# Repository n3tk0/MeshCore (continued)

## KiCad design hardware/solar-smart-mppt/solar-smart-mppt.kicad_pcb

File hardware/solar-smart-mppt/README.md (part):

# solar-smart-mppt: MPPT charger + BMS 1S/2S + coulomb counter

A stand-alone power board for a solar repeater (any board: RAK, XIAO, ProMicro…), grown out
of [`../xiao-solar-lite`](../xiao-solar-lite): the same BQ25798 MPPT buck-boost charger, but the
XIAO stack is gone and a **TI MSPM0L1306** supervisor (VQFN-24, 64 KB flash) runs everything:

- drives the BQ25798 on its own I2C bus (hardware I2C1 master, PA15/PA16),
- shows itself to the repeater as an **INA260 on 0x41** (hardware I2C0 target, PA0/PA1 → J5; the ROM BSL I2C sits on the same pins),
  so MeshCore reads voltage, current and charge with `ENV_INCLUDE_INA260` and no firmware change,
- counts the charge through a 20 mΩ shunt: both shunt ends go through the zero-drift OPA0/OPA1
  (PGA up to 32×) into the 12-bit ADC,
- is the BMS: discharge FET (OD) and charge FET (OC) of an HJ8205 in the battery minus,
  short-circuit cut-off with COMP0 (32 ns) against its 8-bit DAC,
- balances a 2S LTO pack (~40 mA per cell),
- shows errors and BMS state on two LEDs on one pin.

30 × 77.5 mm (three across a 100 mm JLC panel), 2 layers, all SMD parts on the top side (JLC assembly), headers by hand.

Status v0.3 (2026-11-04): schematic, placement, routing, Gerber, JLC BOM/CPL, 3-up panel. ERC: no errors,
DRC: 0 unconnected, no clearance or short errors (only cosmetic items left, see Layout).
**Not built or tested.** Firmware for the MSPM0 (TI MSPM0 SDK, C) is a separate task.

v0.3 is the cost version (JLC quote for 15 boards was 213.63 €; v0.3 is about 150 €, see the cost
note `/mnt/project-files/notes/solar-smart-mppt-v03-cost-2026-11-04.md`):
LTC4412 → discrete ideal diode, ATtiny3226 (89 in stock at JLC) → MSPM0L1306, 2N7002DW → 2 × 2N7002,
MMDT3906 → 2 × MMBT3906, balance resistors 47 Ω → 100 Ω, C9 → 0603, RS1 → RLS12FTCR020: 7 extended
part types with a fee instead of 9.

Decisions: `/mnt/project-files/notes/solar-smart-mppt-phase1-2026-11-03.md` (phase 1) and the
answers in the project thread (phase 2).

## Connections
| Where | Pins | Notes |
|---|---|---|
| J1 SOLAR | + / − | 5–22 V panel (Voc up to 25 V), SS54 against reverse polarity, SMBJ24A TVS |
| J4 BATTERY | BATT+, BM, BATT− | 1S Li-ion / LiFePO4: BATT+ and BATT−, BM open. 2S LTO: BM = middle point |
| J3 NTC | TS / GND | optional 10k NTC (103AT); without it the MCU sets `TS_IGNORE` |
| J6 OUT | + / − | SYS through a discrete ideal diode (Q5 AO3401A + Q9/Q11 MMBT3906): battery or charger voltage, up to 5.6 V with LTO |
| J7 U | + / − | TPS63070 buck-boost, 3.3 V or 5.0 V (JP6), on/off by JP5 |
| J5 I2C host | SCL SDA 3V3 GND | to the repeater; **no pull-ups on this board** (the repeater has them); 3V3 is not used here; PA0/PA1 are 5 V tolerant open-drain pins, and the ROM bootloader (BSL, I2C) listens on them, so the host can also flash the MCU over J5: a blank chip starts the BSL by itself, a programmed one on `smppt cmd bsl`; a chip with broken firmware needs SWD (the BSL invoke pin PA18 is not on J5) |
| TP12, TP13, TP11, TP16, TP17 | 3V3M, GND, SWDIO, SWCLK, NRST | SWD on the **bottom side**, one row at 2.54 mm under the MCU band, left to right seen from the top (a 5-pin header or pogo pins from below) |

## Jumpers
| Jumper | Open | 1-2 | 2-3 |
|---|---|---|---|
| JP4 CHEM | Li-ion (PA23 follows the internal pull) | LiFePO4 (always 0) | LTO 2S (always 1) |
| JP5 EN of J7 | off | always on | MCU PA4 switches it |
| JP6 VSEL of J7 | 3.3 V | closed = 5.0 V | |
| JP3 | ship FET Q2 in use | closed = no ship FET | |

## How it works
- **Charger:** BQ25798, PROG always 1S (R1 4.7k, 750 kHz). With a 2S PROG the chip would start
  with VSYSMIN ≈ 7 V, too much for the 5.5 V parts on SYS. For LTO the MCU writes VREG 5.6 V
  (2.8 V/cell) and only then pulls ~CE low (PA17). ~CE has a pull-up to 3V3M (R4): no MCU, no charging.
  INT is not connected; the MCU polls.
- **3V3M:** HT7533 (2.5 µA) from SYS, only for the MCU and its dividers. VDD 10 µF + 100 nF,
  VCORE 470 nF, NRST 47k + 10 nF (TI minimum circuit).
- **Ideal diode (J6):** Q5 (P-FET, D at SYS, S at J6) conducts SYS → OUT through its body diode
  and is switched fully on by the PNP mirror: Q9 (diode connected, E at SYS) sets the base, Q11
  (E at OUT) pulls the Q5 gate to OUT as soon as OUT rises above SYS, so a load with its own supply
  (USB on a XIAO) cannot feed back into the battery. R43 1 MΩ / R44 470 kΩ: ~4 µA; Q5 is fully on already at 0 V drop (gate ~1.5 V at 3.7 V), and turns off when OUT is ~25 mV above SYS (up to ~0.4 A reverse for that moment).
- **BMS (Q3 HJ8205 in BATT−):** S1 = cell minus, S2 → shunt RS1 → GND.
  OD (discharge, G1) is **on by default** through R18 to BATT+, so SYS starts from the battery alone;
  the MCU turns it off through Q6 (PA26, no MCU pin sees BATT+). OC (charge, G2) is on as soon as
  3V3M is up (R20) and the MCU turns it off (PA10).
  Under-voltage uses the BQ25798 ship mode (Q2, SDRV): sun on VBUS wakes the charger, SYS comes back
  and the MCU starts again. There is **no DW01A**: over-current and short are handled by the MCU
  (OPA + COMP0 with the DAC threshold) and by the BQ25798 BATFET OCP.
- **Shunt:** 20 mΩ 1 % (±3.2 A). R21/R22 (10k) take Kelvin taps from both shunt ends, R23/R24 (1M to 3V3M)
  lift both inputs by ~33 mV so they stay above 0 V while discharging, C24 100 nF across them.
  The GND-end tap is a real Kelvin connection: R22 sits on its own net SH_K, joined to the RS1 GND
  pad by the net tie NT1, so load current in the GND pour does not shift the reading.
  SH_P runs straight down from the MCU on F.Cu with SH_N under it on B.Cu (a pair).
  SH_P → PA25 (OPA0 IN+), SH_N → PA18 (OPA1 IN+). Positive = charging.
  The offset is calibrated at zero current. Firmware: keep the OPA1 output pin off (PA16 is I2C1 SDA)
  and the OPA0 output pin PA22 unused; PA18 is also the BSL pin and sits at ~33 mV at reset (no BSL).
- **Dividers:** VBAT 1M/470k (PA24, A3), BM 1M/1M (PA21, A5), both with 100 nF. Highest ADC input is ~1.79 V
  (VBAT at 5.6 V, 2S LTO) and ~1.4 V (BM), so the firmware uses the internal 2.5 V VREF (1.4 V would clip).
- **CHEM jumper (JP4 → PA23):** read twice, once with the internal pull-up and once with the pull-down.
- **Balancing:** cell 1 (BATT−..BM) through Q7 (PA2) + R37 100 Ω; cell 2 (BM..BATT+) through the P-FET Q8
  + R41 100 Ω, its gate pulled down by Q10 (PA3). Both need push-pull pins. ~40 mA at 4.2 V, 0.18 W per 1206. Only for 2S.
- **LEDs (PA9):** high = red D6 (error), low = yellow D7 (BMS / balancing), Hi-Z = both off
  (1.8 + 1.9 V > 3.3 V, no current).
- **J7:** TPS63070 (2–16 V in), L2 2.2 µH (same part as L1) + 10 µF + 3 × 22 µF (TI table 3: Cout,eff ≥ 10 × L,eff). FB R33/R34 = 3.3 V, VSEL high adds
  R35 in parallel to R34 = 5.0 V. EN, VSEL and PS/SYNC go to VIN only through R30 10k (TI 11.1).
  PS/SYNC high = power save at light load.

## MCU pins (MSPM0L1306SRGER, VQFN-24)
| Pin | Port | Net | Use |
|---|---|---|---|
| 24 / 1 | PA0 / PA1 | SDA_E / SCL_E | I2C0 target (INA260 0x41) → J5, open-drain 5 V tolerant, also the ROM BSL I2C (SDA / SCL) |
| 12 / 11 | PA16 / PA15 | SDA_I / SCL_I | I2C1 controller → BQ25798 (R13/R14 4.7k) |
| 21 / 14 | PA25 / PA18 | SH_P / SH_N | OPA0 / OPA1 IN+ (shunt) |
| 20 / 17 | PA24 / PA21 | ADC_VBAT / ADC_VBM | ADC A3 / A5 |
| 19 | PA23 | ADC_CHEM | JP4 (digital) |
| 13 | PA17 | CE | ~CE low = charge (R4 pull-up) |
| 9 | PA10 | OC_G | R20 pull-up to 3V3M: low = charge FET off (push-pull; driving it high gives the same 3.3 V as R20) |
| 22 | PA26 | OD_CTL | discharge FET off (Q6) |
| 5 / 6 | PA2 / PA3 | BAL1 / BAL2 | balancing |
| 8 | PA9 | LED | D6 / D7 |
| 7 | PA4 | REG_CTL | J7 EN through JP5 2-3 |
| 10 | PA11 | – | not connected |
| 18 | PA22 | – | OPA0 output pin, not connected (keep the OPA0 output off the pin) |
| 15 / 16 / 2 | PA19 / PA20 / NRST | SWD | TP11 / TP16 / TP17 |
| 3 / 23 / 4, EP | VDD / VCORE / VSS | | 3V3M, 470 nF, GND (4 vias in the EP, tented from below) |

The pins are grouped by direction so every pin leaves the package without crossing: up (OC_G, LED, J7 EN),
left (CE, SWD, SH_N, VBM), down (CHEM, VBAT, SH_P, OD, VCORE, J5 SDA), right (balancing, NRST, J5 SCL).

## Layout
- Charger part = the xiao-solar-lite layout (shared cluster `../xiao-solar/tools/charger.py`).
- TPS63070 after the TI layout example: inductor above the IC, SW nodes as short copper, VIN caps left,
  VOUT caps right, PGND and GND joined under the package and taken to two vias.
- Top row: J6 OUT | J5 I2C | J7 U, ideal diode under J6, jumpers JP5/JP6 under J7.
- MCU band under the charger: MSPM0 turned 180°, its fan-out drawn by hand (`MCU_STUBS` in
  `tools/gen_pcb.py`): SWD row and HT7533 on the left, BM / VBAT dividers and JP4 under the MCU,
  balancing FETs Q8/Q10 on the right next to R37/R41.
- Shunt filter (C24, R21–R24) and net tie NT1 at the shunt RS1; SH_P on F.Cu, SH_N under it on B.Cu.
- MLCCs keep ≥ 0.9 mm from the V-cut edges (C21 and C20 turned parallel to the cut); U5, Q5, Q9, D1 pads ≥ 1.5 mm from the left edge.
- BMS, shunt, fuse at the bottom next to J4.

## Files and tools
- `tools/gen_sch.py`: schematic + BOM, writer from `../xiao-solar/tools/gen_sch.py`.
  This board has its own copy of the symbol/footprint library in `lib/` (TPS63070, HT7533 from
  easyeda2kicad); MSPM0, MMBT3906 and 2N7002 use the KiCad standard footprints.
- `tools/gen_pcb.py`: placement, TPS63070 copper, outline, pours, and the locked pre-routes:
  SYS (0.8 mm), the long MCU lines (`PRE_ROUTES`), fixed TPS63070/BQ25798 hand routes
  (`tools/hand_routes.json`, kept from v0.2) and a GND tie (short track + via into the
  B.Cu fill) for every small GND pad that the F.Cu pour cannot reach. `B_CLEAR` boxes keep
  Freerouting off B.Cu where long B lines used to cut the ground fill into islands.
- `tools/patch2.py`: own two-layer grid A* (0.1 mm grid). Used for the pre-routes and for the few
  connections Freerouting leaves open: `python3 tools/patch2.py NET X1 Y1 X2 Y2 [WIDTH]`.
- `tools/gndfix.py`, `tools/bfrag.py`: check for GND copper without a connection and tie it with a via.
- `tools/run.py <tool>` runs a shared tool from `../xiao-solar/tools` on this board:
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
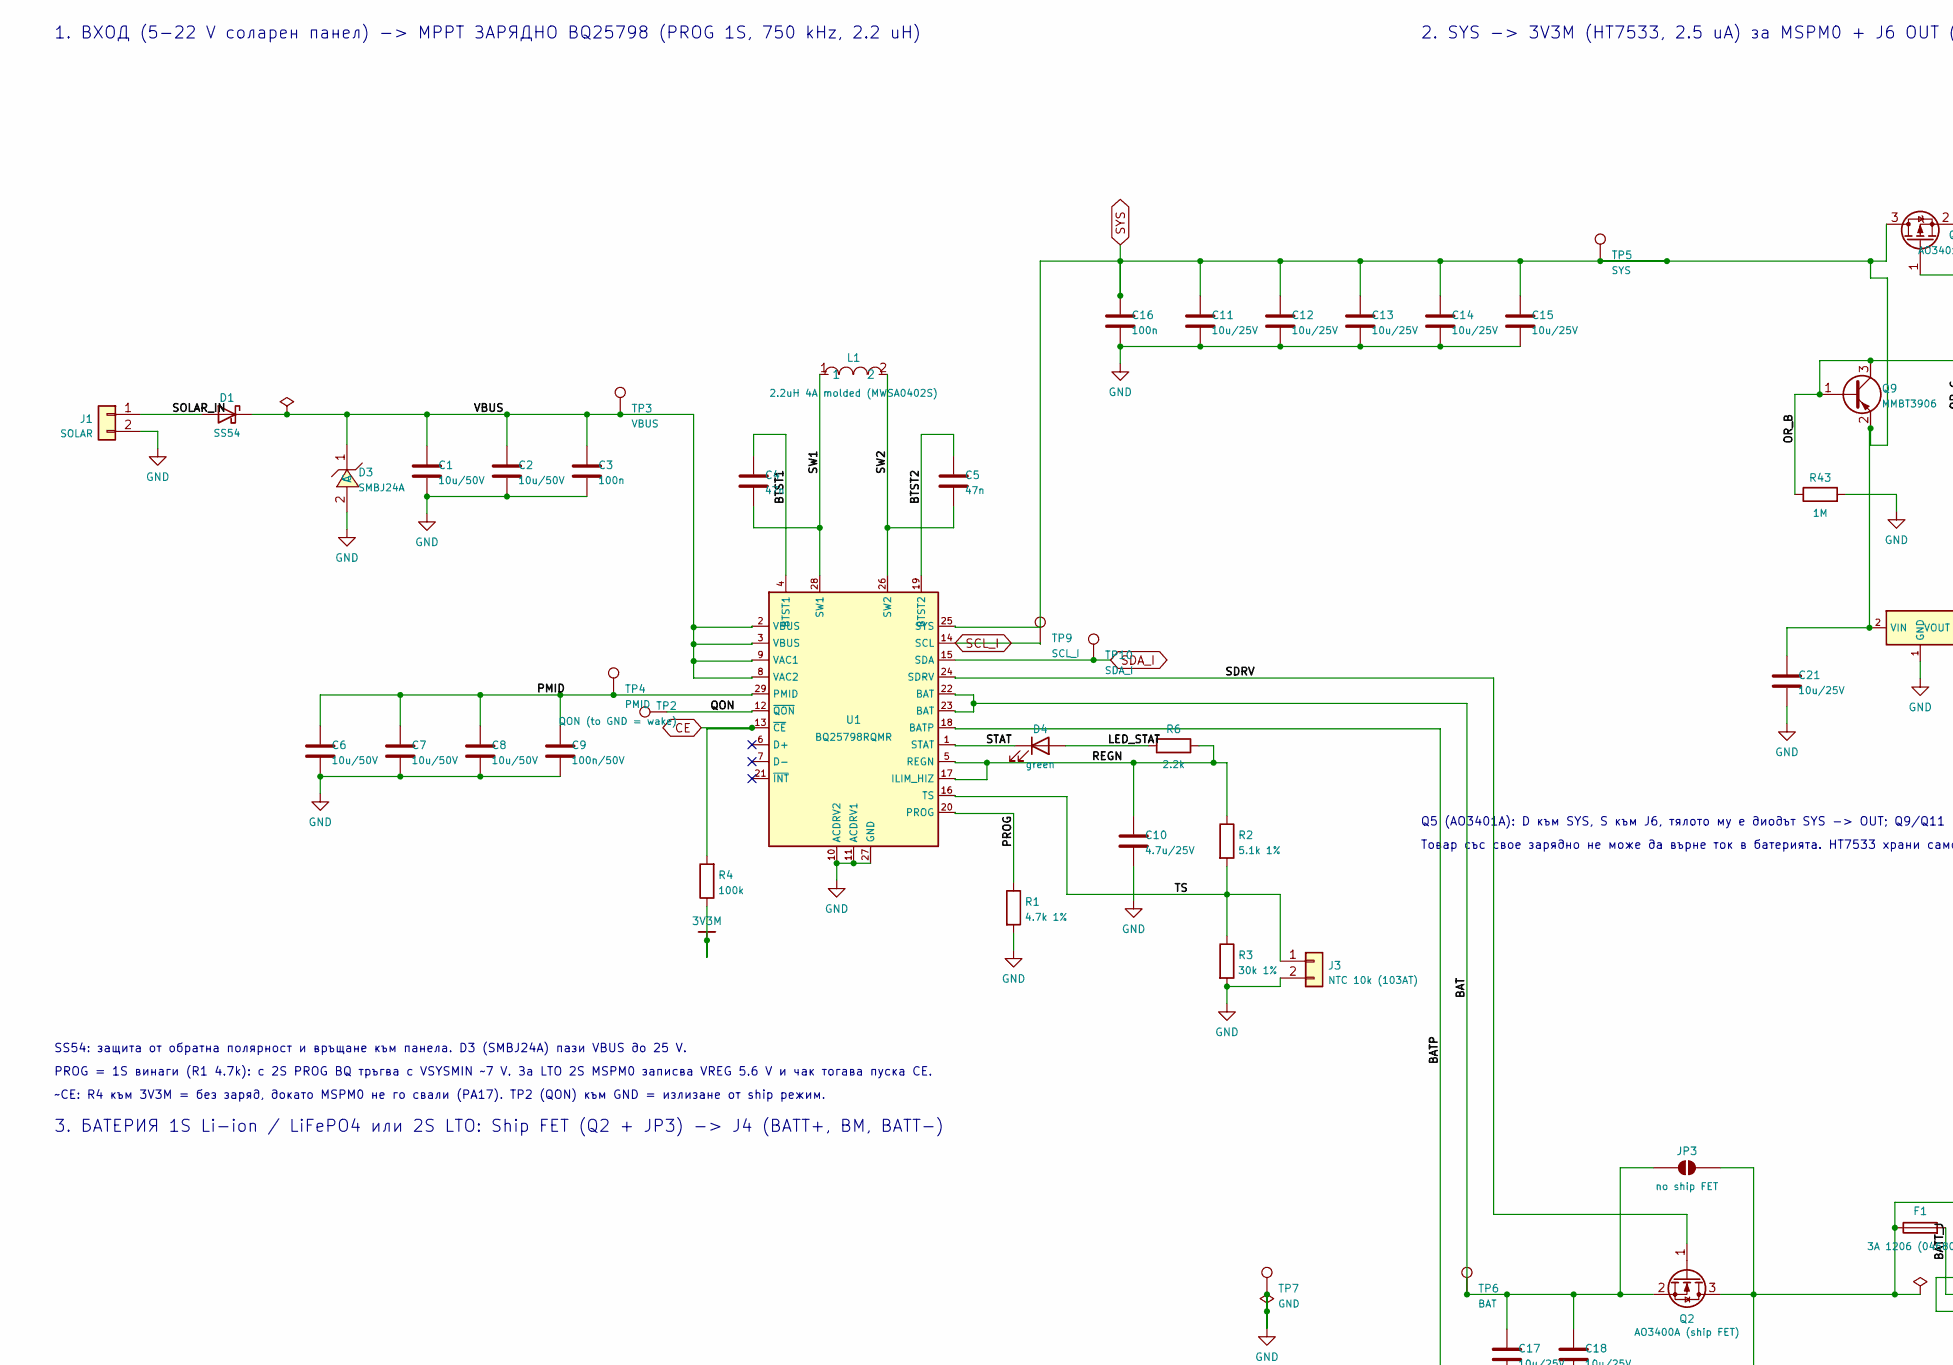
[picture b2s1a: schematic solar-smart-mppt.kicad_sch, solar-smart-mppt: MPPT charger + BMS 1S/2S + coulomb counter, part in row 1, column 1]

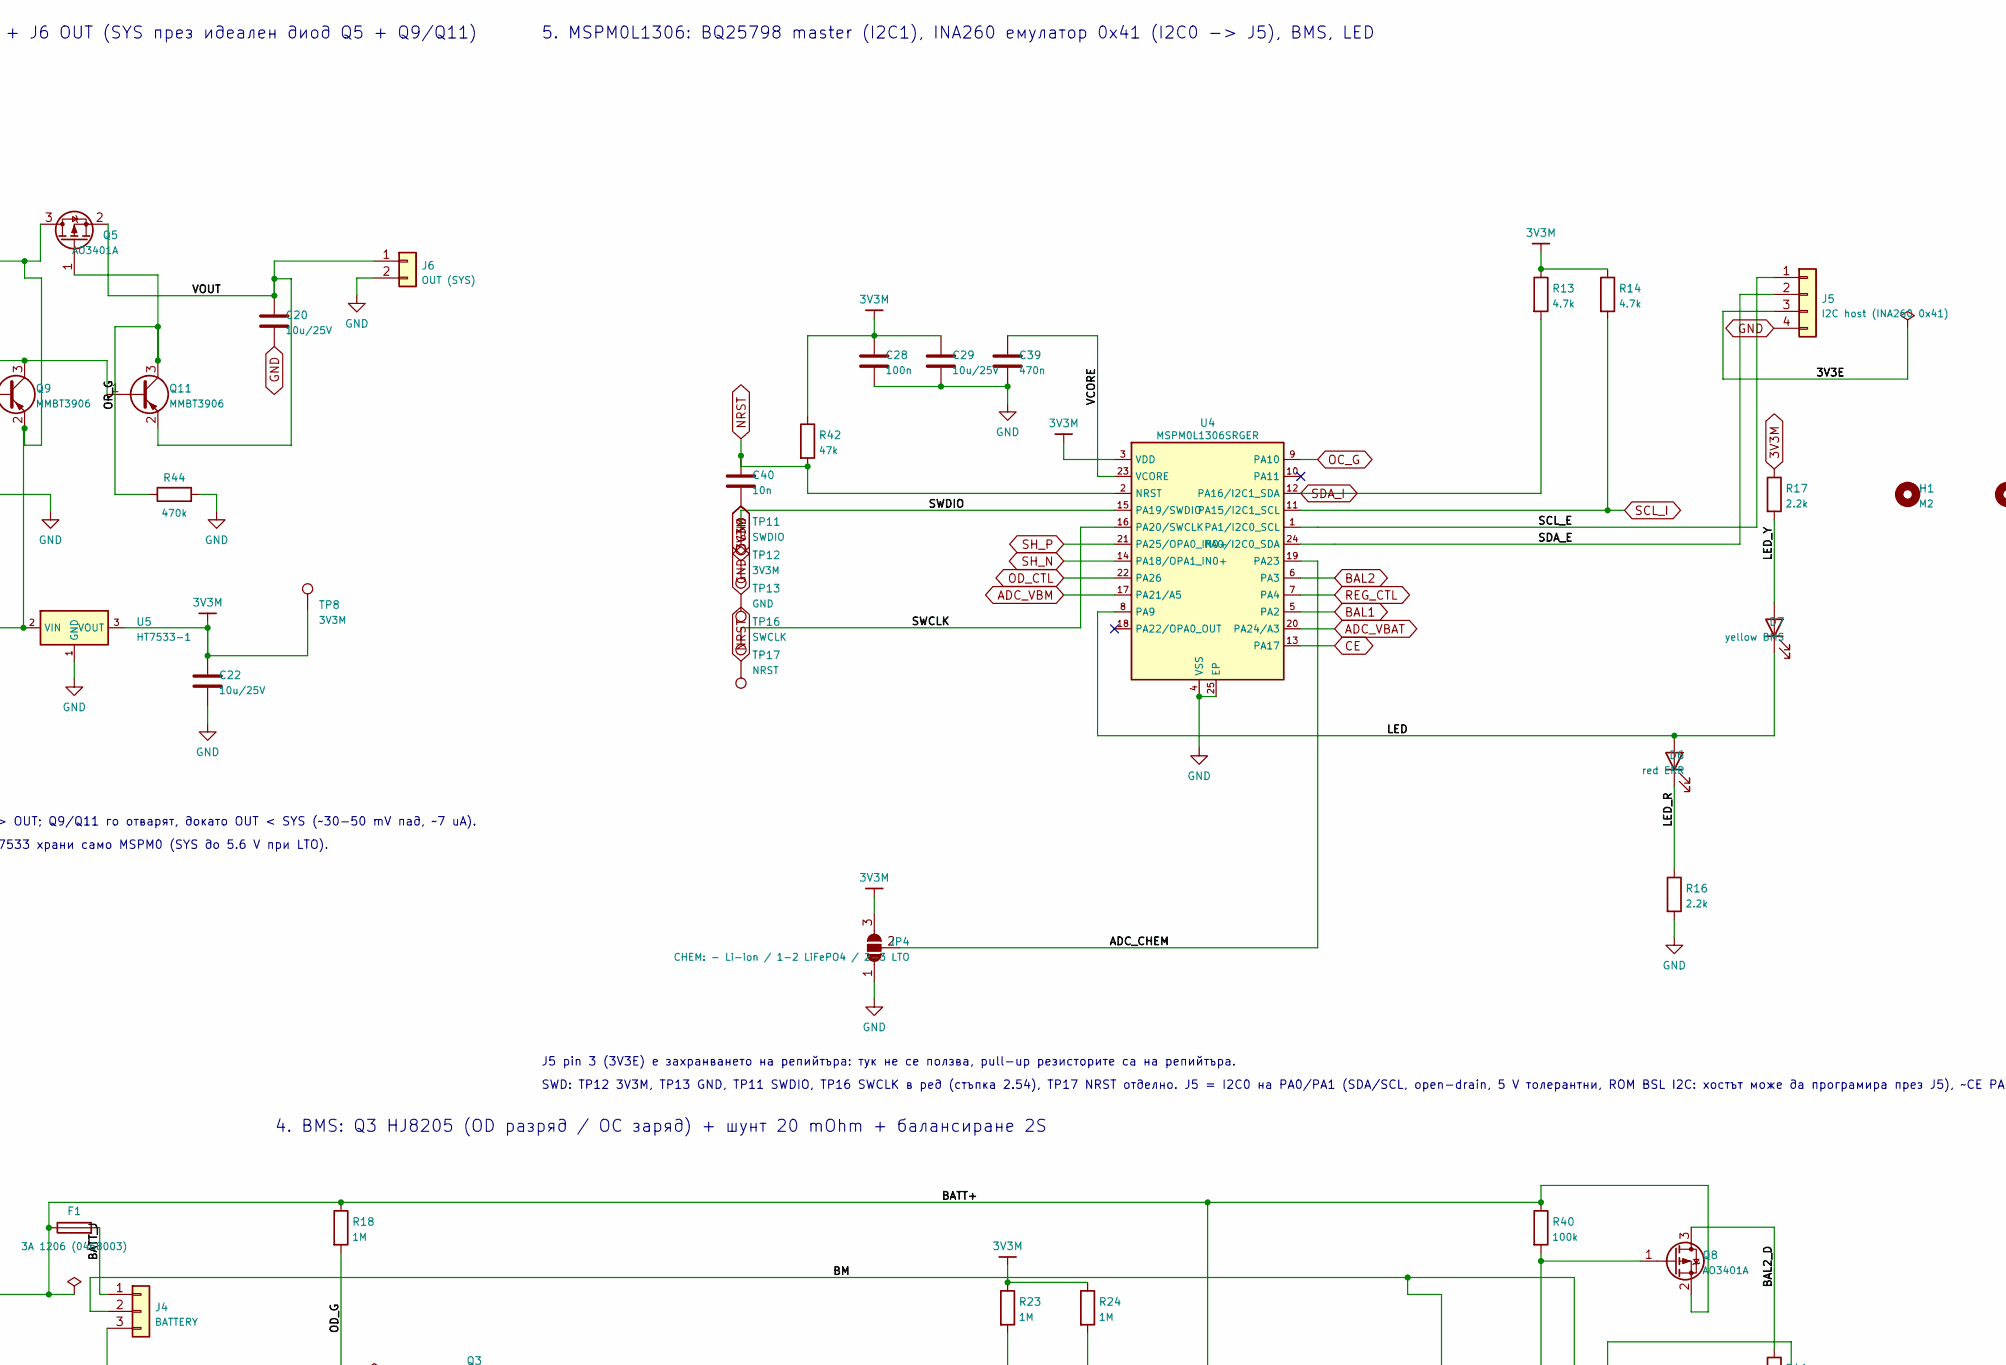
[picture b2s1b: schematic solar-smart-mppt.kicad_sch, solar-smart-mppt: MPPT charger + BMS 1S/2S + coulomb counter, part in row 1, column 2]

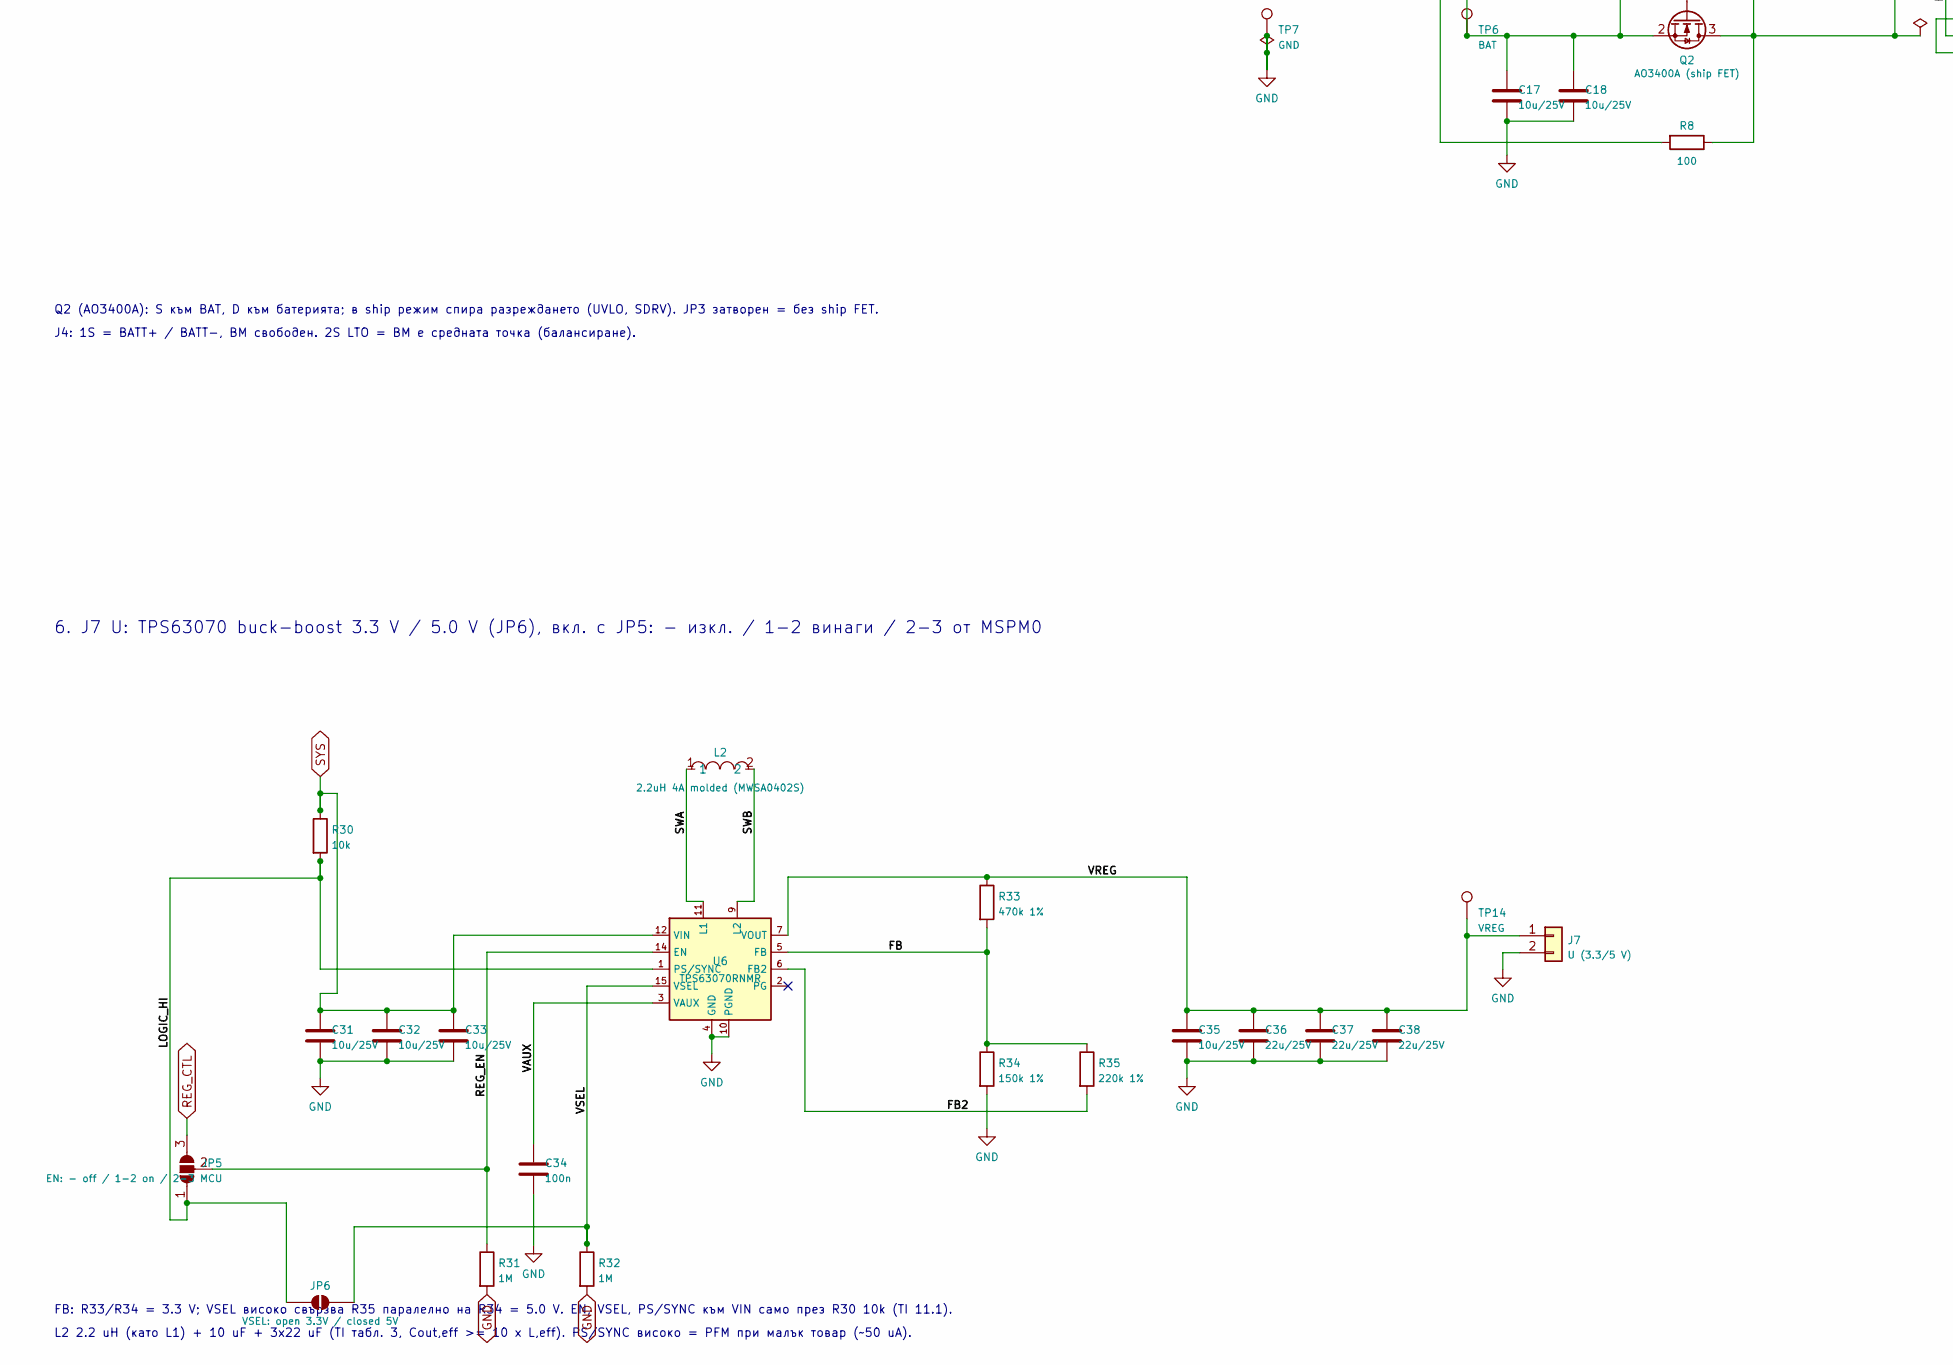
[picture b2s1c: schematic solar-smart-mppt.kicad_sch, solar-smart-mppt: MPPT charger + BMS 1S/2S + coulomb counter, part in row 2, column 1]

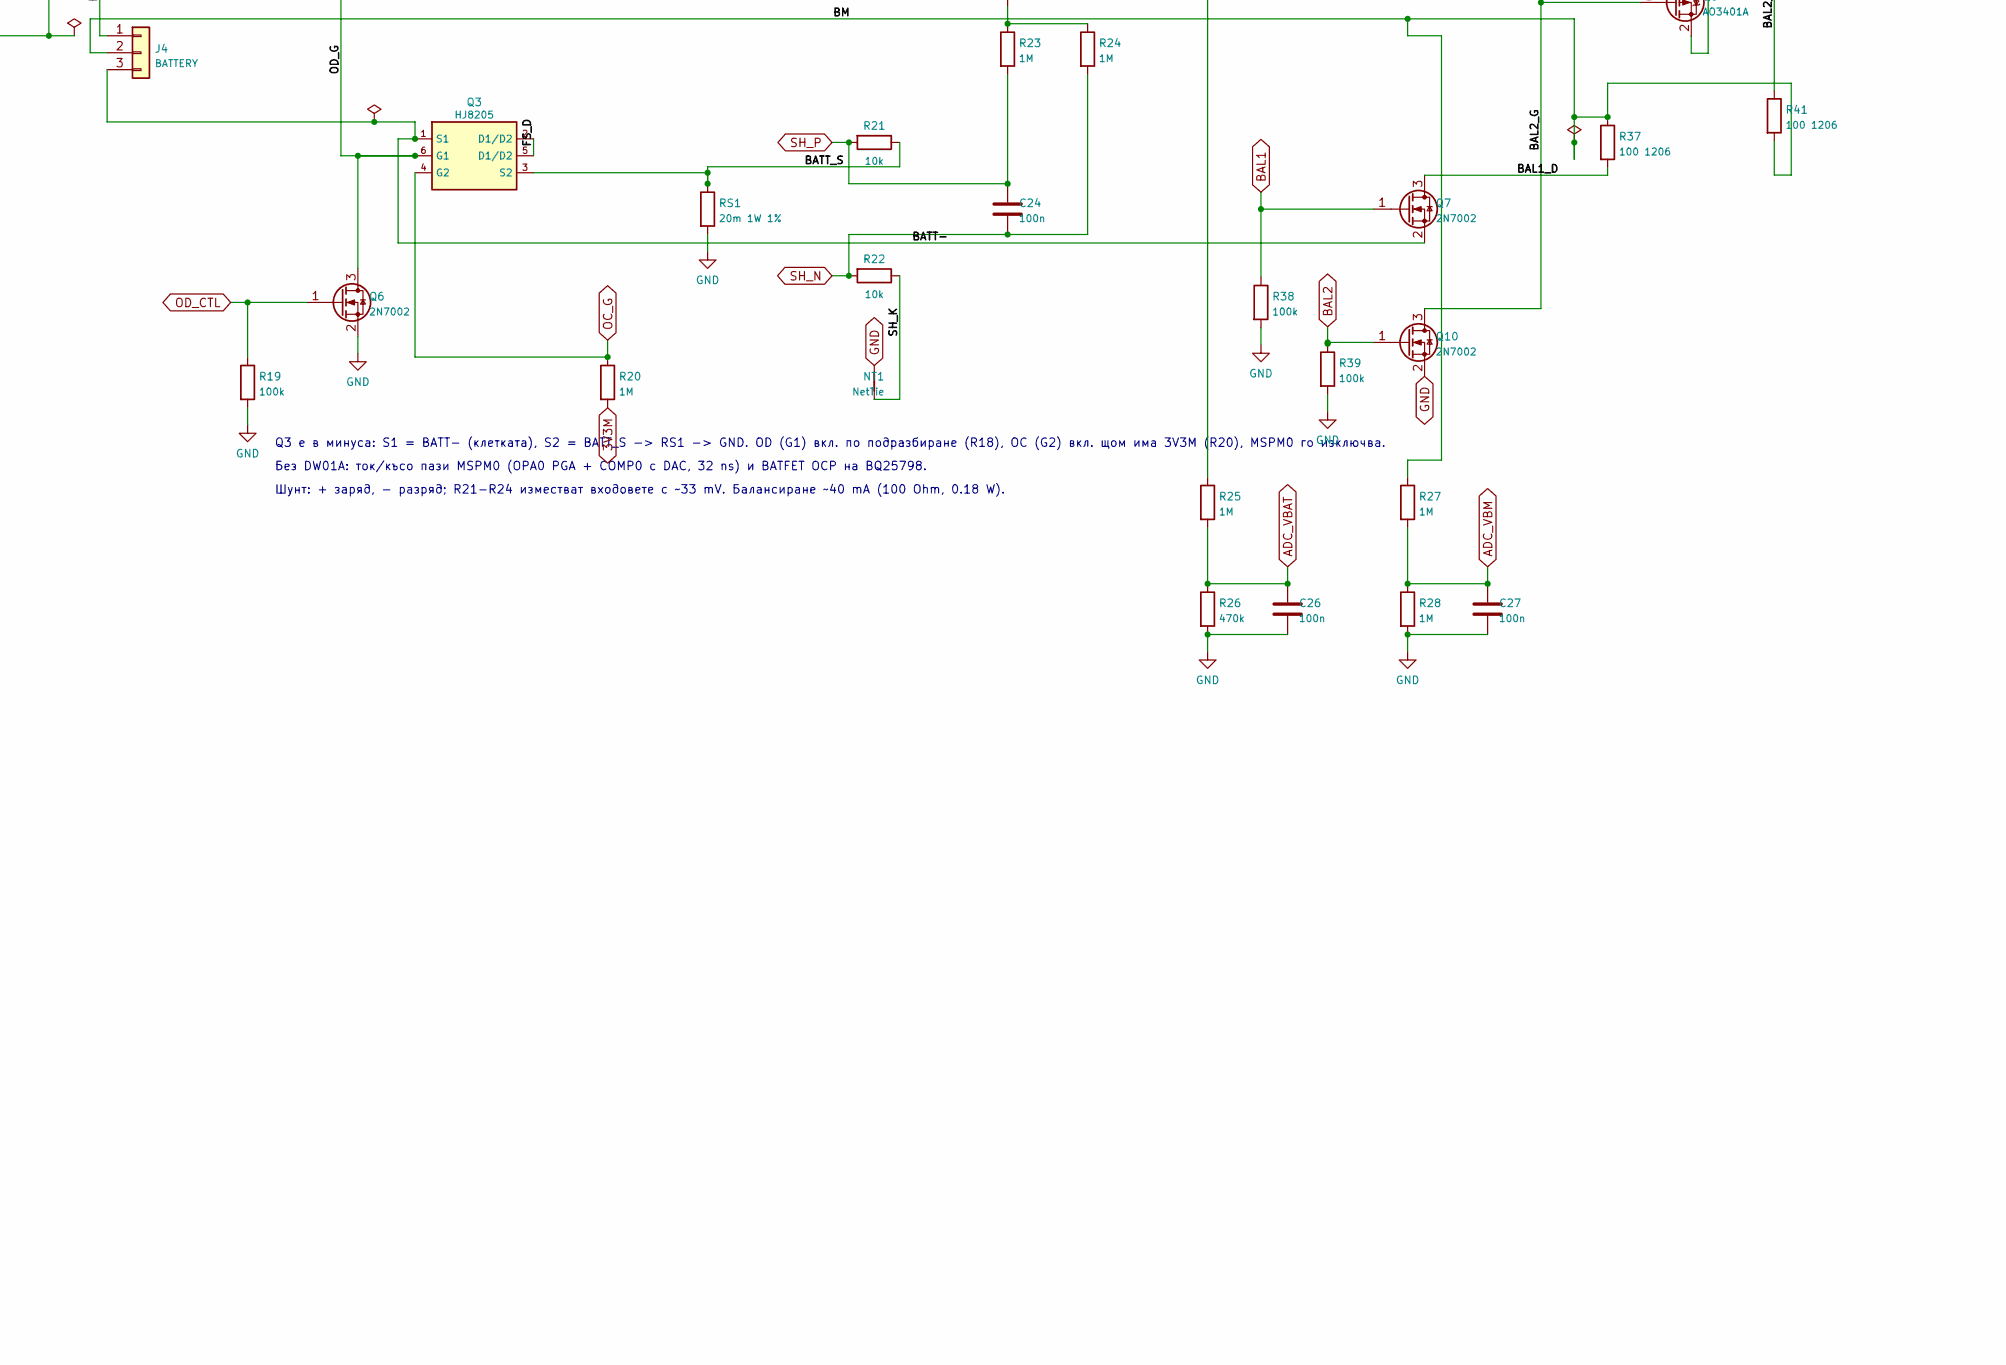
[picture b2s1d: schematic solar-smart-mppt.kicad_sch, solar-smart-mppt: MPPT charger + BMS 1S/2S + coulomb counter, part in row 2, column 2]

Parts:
C1, C2, C6, C7, C8: 10u/50V; C_1206_3216Metric; LCSC C13585
C3: 100n; C_0603_1608Metric; LCSC C14663
C4, C5: 47n; C_0603_1608Metric; LCSC C1622
C9: 100n/50V; C_0603_1608Metric; LCSC C14663
C10: 4.7u/25V; C_0805_2012Metric; LCSC C1779
C11, C12, C13, C14, C15, C17, C18, C20, C21, C22, C29, C31, C32, C33, C35: 10u/25V; C_0805_2012Metric; LCSC C15850
C16, C24, C26, C27, C28, C34: 100n; C_0402_1005Metric; LCSC C1525
C36, C37, C38: 22u/25V; C_0805_2012Metric; LCSC C45783
C39: 470n; C_0603_1608Metric; LCSC C1623
C40: 10n; C_0402_1005Metric; LCSC C15195
D1: SS54; D_SMA; LCSC C22452
D3: SMBJ24A; SMB_L4.6-W3.6-LS5.3-RD; LCSC C19077578
D4: green; LED_0805_2012Metric; LCSC C2297
D6: red ERR; LED_0805_2012Metric; LCSC C84256
D7: yellow BMS; LED_0805_2012Metric; LCSC C2296
F1: 3A 1206 (0468003); Fuse_1206_3216Metric; LCSC C41342
H1, H2: M2; MountingHole_2.2mm_M2
J1: SOLAR; PinHeader_1x02_P2.54mm_Vertical
J3: NTC 10k (103AT); PinHeader_1x02_P2.54mm_Vertical
J4: BATTERY; PinHeader_1x03_P2.54mm_Vertical
J5: I2C host (INA260 0x41); PinHeader_1x04_P2.54mm_Vertical
J6: OUT (SYS); PinHeader_1x02_P2.54mm_Vertical
J7: U (3.3/5 V); PinHeader_1x02_P2.54mm_Vertical
JP3: no ship FET; SolderJumper-2_P1.3mm_Open_RoundedPad1.0x1.5mm
JP4: CHEM: - Li-ion / 1-2 LiFePO4 / 2-3 LTO; SolderJumper-3_P1.3mm_Open_RoundedPad1.0x1.5mm
JP5: EN: - off / 1-2 on / 2-3 MCU; SolderJumper-3_P1.3mm_Open_RoundedPad1.0x1.5mm
JP6: VSEL: open 3.3V / closed 5V; SolderJumper-2_P1.3mm_Open_RoundedPad1.0x1.5mm
L1, L2: 2.2uH 4A molded (MWSA0402S); IND-SMD_L4.4-W4.2_MWSA0402S; LCSC C408335
NT1: NetTie; NetTie-2_SMD_Pad0.5mm
Q2: AO3400A (ship FET); SOT-23; LCSC C20917
Q3: HJ8205; SOT-23-6_L2.9-W1.6-P0.95-LS2.8-BL; LCSC C20069150
Q5, Q8: AO3401A; SOT-23; LCSC C15127
Q6, Q7, Q10: 2N7002; SOT-23; LCSC C8545
Q9, Q11: MMBT3906; SOT-23; LCSC C7420354
R1: 4.7k 1%; R_0603_1608Metric; LCSC C23162
R2: 5.1k 1%; R_0603_1608Metric; LCSC C23186
R3: 30k 1%; R_0603_1608Metric; LCSC C22984
R4, R19, R38, R39, R40: 100k; R_0402_1005Metric; LCSC C25741
R6, R16, R17: 2.2k; R_0402_1005Metric; LCSC C25879
R8: 100; R_0603_1608Metric; LCSC C22775
R13, R14: 4.7k; R_0402_1005Metric; LCSC C25900
R18, R20, R23, R24, R25, R27, R28, R31, R32, R43: 1M; R_0402_1005Metric; LCSC C26083
R21, R22, R30: 10k; R_0402_1005Metric; LCSC C25744
R26, R44: 470k; R_0603_1608Metric; LCSC C23178
R33: 470k 1%; R_0603_1608Metric; LCSC C23178
R34: 150k 1%; R_0603_1608Metric; LCSC C22807
R35: 220k 1%; R_0603_1608Metric; LCSC C22961
R37, R41: 100 1206; R_1206_3216Metric; LCSC C17901
R42: 47k; R_0402_1005Metric; LCSC C25792
RS1: 20m 1W 1%; R_1206_3216Metric; LCSC C163047
TP2: QON (to GND = wake); TestPoint_Pad_D1.0mm
TP3: VBUS; TestPoint_Pad_D1.0mm
TP4: PMID; TestPoint_Pad_D1.0mm
TP5: SYS; TestPoint_Pad_D1.0mm
TP6: BAT; TestPoint_Pad_D1.0mm
TP7, TP13: GND; TestPoint_Pad_D1.0mm
TP8, TP12: 3V3M; TestPoint_Pad_D1.0mm
TP9: SCL_I; TestPoint_Pad_D1.0mm
TP10: SDA_I; TestPoint_Pad_D1.0mm
TP11: SWDIO; TestPoint_Pad_D1.0mm
TP14: VREG; TestPoint_Pad_D1.0mm
TP16: SWCLK; TestPoint_Pad_D1.0mm
TP17: NRST; TestPoint_Pad_D1.0mm
U1: BQ25798RQMR; QFN-29_L4.0-W4.0-P0.40-TL-BQ25792RQMR; LCSC C2876593
U4: MSPM0L1306SRGER; VQFN-24-1EP_4x4mm_P0.5mm_EP2.45x2.45mm; LCSC C19189323
U5: HT7533-1; SOT-89-3_L4.5-W2.5-P1.50-LS4.2-BR; LCSC C14289
U6: TPS63070RNMR; VQFN-15_L3.0-W2.5-P0.50-BL; LCSC C109322

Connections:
3V3E: J5.3
3V3M: C22.1, C28.1, C29.1, JP4.3 (B), R4.1, R13.1, R14.1, R17.1, R20.2, R23.1, R24.1, R42.1, TP8.1, TP12.1, U4.3 (VDD), U5.3 (VOUT)
ADC_CHEM: JP4.2 (C), U4.19 (PA23)
ADC_VBAT: C26.1, R25.2, R26.1, U4.20 (PA24/A3)
ADC_VBM: C27.1, R27.2, R28.1, U4.17 (PA21/A5)
BAL1: Q7.1 (G), R38.1, U4.5 (PA2)
BAL1_D: Q7.3 (D), R37.2
BAL2: Q10.1 (G), R39.1, U4.6 (PA3)
BAL2_D: Q8.3 (D), R41.1
BAL2_G: Q8.1 (G), Q10.3 (D), R40.2
BAT: C17.1, C18.1, JP3.1 (A), Q2.2 (S), TP6.1, U1.22 (BAT), U1.23 (BAT)
BATP: R8.2, U1.18 (BATP)
BATT+: F1.1, JP3.2 (B), Q2.3 (D), Q8.2 (S), R8.1, R18.1, R25.1, R40.1
BATT-: J4.3, Q3.1 (S1), Q7.2 (S)
BATT_J: F1.2, J4.1
BATT_S: Q3.3 (S2), R21.1, RS1.1
BM: J4.2, R27.1, R37.1, R41.2
BTST1: C4.1, U1.4 (BTST1)
BTST2: C5.1, U1.19 (BTST2)
CE: R4.2, U1.13 (~CE), U4.13 (PA17)
FB: R33.2, R34.1, R35.1, U6.5 (FB)
FB2: R35.2, U6.6 (FB2)
FS_D: Q3.2 (D1/D2), Q3.5 (D1/D2)
GND: C1.2, C2.2, C3.2, C6.2, C7.2, C8.2, C9.2, C10.2, C11.2, C12.2, C13.2, C14.2, C15.2, C16.2, C17.2, C18.2, C20.2, C21.2, C22.2, C26.2, C27.2, C28.2, C29.2, C31.2, C32.2, C33.2, C34.2, C35.2, C36.2, C37.2, C38.2, C39.2, C40.2, D3.2 (A), J1.2, J3.2, J5.4, J6.2, J7.2, JP4.1 (A), NT1.2, Q6.2 (S), Q10.2 (S), R1.2, R3.2, R16.2, R19.2, R26.2, R28.2, R31.2, R32.2, R34.2, R38.2, R39.2, R43.2, R44.2, RS1.2, TP7.1, TP13.1, U1.10 (ACDRV2), U1.11 (ACDRV1), U1.27 (GND), U4.4 (VSS), U4.25 (EP), U5.1 (GND), U6.4 (GND), U6.10 (PGND)
LED: D6.2 (A), D7.1 (K), U4.8 (PA9)
LED_R: D6.1 (K), R16.1
LED_STAT: D4.2 (A), R6.2
LED_Y: D7.2 (A), R17.2
LOGIC_HI: JP5.1 (A), JP6.1 (A), R30.2, U6.1 (PS/SYNC)
NRST: C40.1, R42.2, TP17.1, U4.2 (NRST)
OC_G: Q3.4 (G2), R20.1, U4.9 (PA10)
OD_CTL: Q6.1 (G), R19.1, U4.22 (PA26)
OD_G: Q3.6 (G1), Q6.3 (D), R18.2
OR_B: Q9.1 (B), Q9.3 (C), Q11.1 (B), R43.1
OR_G: Q5.1 (G), Q11.3 (C), R44.1
PMID: C6.1, C7.1, C8.1, C9.1, TP4.1, U1.29 (PMID)
PROG: R1.1, U1.20 (PROG)
QON: TP2.1, U1.12 (~QON)
REGN: C10.1, R2.1, R6.1, U1.5 (REGN), U1.17 (ILIM_HIZ)
REG_CTL: JP5.3 (B), U4.7 (PA4)
REG_EN: JP5.2 (C), R31.1, U6.14 (EN)
SCL_E: J5.1, U4.1 (PA1/I2C0_SCL)
SCL_I: R14.2, TP9.1, U1.14 (SCL), U4.11 (PA15/I2C1_SCL)
SDA_E: J5.2, U4.24 (PA0/I2C0_SDA)
SDA_I: R13.2, TP10.1, U1.15 (SDA), U4.12 (PA16/I2C1_SDA)
SDRV: Q2.1 (G), U1.24 (SDRV)
SH_K: NT1.1, R22.1
SH_N: C24.2, R22.2, R24.2, U4.14 (PA18/OPA1_IN0+)
SH_P: C24.1, R21.2, R23.2, U4.21 (PA25/OPA0_IN0+)
SOLAR_IN: D1.2 (A), J1.1
STAT: D4.1 (K), U1.1 (STAT)
SW1: C4.2, L1.1, U1.28 (SW1)
SW2: C5.2, L1.2, U1.26 (SW2)
SWA: L2.1, U6.11 (L1)
SWB: L2.2, U6.9 (L2)
SWCLK: TP16.1, U4.16 (PA20/SWCLK)
SWDIO: TP11.1, U4.15 (PA19/SWDIO)
SYS: C11.1, C12.1, C13.1, C14.1, C15.1, C16.1, C21.1, C31.1, C32.1, C33.1, Q5.3 (D), Q9.2 (E), R30.1, TP5.1, U1.25 (SYS), U5.2 (VIN), U6.12 (VIN)
TS: J3.1, R2.2, R3.1, U1.16 (TS)
VAUX: C34.1, U6.3 (VAUX)
VBUS: C1.1, C2.1, C3.1, D1.1 (K), D3.1 (C), TP3.1, U1.2 (VBUS), U1.3 (VBUS), U1.8 (VAC2), U1.9 (VAC1)
VCORE: C39.1, U4.23 (VCORE)
VOUT: C20.1, J6.1, Q5.2 (S), Q11.2 (E)
VREG: C35.1, C36.1, C37.1, C38.1, J7.1, R33.1, TP14.1, U6.7 (VOUT)
VSEL: JP6.2 (B), R32.1, U6.15 (VSEL)

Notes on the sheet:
1. ВХОД (5-22 V соларен панел) -> MPPT ЗАРЯДНО BQ25798 (PROG 1S, 750 kHz, 2.2 uH)
SS54: защита от обратна полярност и връщане към панела. D3 (SMBJ24A) пази VBUS до 25 V.
PROG = 1S винаги (R1 4.7k): с 2S PROG BQ тръгва с VSYSMIN ~7 V. За LTO 2S MSPM0 записва VREG 5.6 V и чак тогава пуска CE.
~CE: R4 към 3V3M = без заряд, докато MSPM0 не го свали (PA17). TP2 (QON) към GND = излизане от ship режим.
2. SYS -> 3V3M (HT7533, 2.5 uA) за MSPM0 + J6 OUT (SYS през идеален диод Q5 + Q9/Q11)
Q5 (AO3401A): D към SYS, S към J6, тялото му е диодът SYS -> OUT; Q9/Q11 го отварят, докато OUT < SYS (~30-50 mV пад, ~7 uA).
Товар със свое зарядно не може да върне ток в батерията. HT7533 храни само MSPM0 (SYS до 5.6 V при LTO).
3. БАТЕРИЯ 1S Li-ion / LiFePO4 или 2S LTO: Ship FET (Q2 + JP3) -> J4 (BATT+, BM, BATT-)
Q2 (AO3400A): S към BAT, D към батерията; в ship режим спира разреждането (UVLO, SDRV). JP3 затворен = без ship FET.
J4: 1S = BATT+ / BATT-, BM свободен. 2S LTO = BM е средната точка (балансиране).
4. BMS: Q3 HJ8205 (OD разряд / OC заряд) + шунт 20 mOhm + балансиране 2S
Q3 е в минуса: S1 = BATT- (клетката), S2 = BATT_S -> RS1 -> GND. OD (G1) вкл. по подразбиране (R18), OC (G2) вкл. щом има 3V3M (R20), MSPM0 го изключва.
Без DW01A: ток/късо пази MSPM0 (OPA0 PGA + COMP0 с DAC, 32 ns) и BATFET OCP на BQ25798.
Шунт: + заряд, - разряд; R21-R24 изместват входовете с ~33 mV. Балансиране ~40 mA (100 Ohm, 0.18 W).
5. MSPM0L1306: BQ25798 master (I2C1), INA260 емулатор 0x41 (I2C0 -> J5), BMS, LED
J5 pin 3 (3V3E) е захранването на репийтъра: тук не се ползва, pull-up резисторите са на репийтъра.
SWD: TP12 3V3M, TP13 GND, TP11 SWDIO, TP16 SWCLK в ред (стъпка 2.54), TP17 NRST отделно. J5 = I2C0 на PA0/PA1 (SDA/SCL, open-drain, 5 V толерантни, ROM BSL I2C: хостът може да програмира през J5), ~CE PA17, OC_G PA10, LED PA9, J7 EN PA4, BAL1 PA2, BAL2 PA3, OD PA26, CHEM PA23, VBAT PA24/A3, VBM PA2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
6. J7 U: TPS63070 buck-boost 3.3 V / 5.0 V (JP6), вкл. с JP5: - изкл. / 1-2 винаги / 2-3 от MSPM0
FB: R33/R34 = 3.3 V; VSEL високо свързва R35 паралелно на R34 = 5.0 V. EN, VSEL, PS/SYNC към VIN само през R30 10k (TI 11.1).
L2 2.2 uH (като L1) + 10 uF + 3x22 uF (TI табл. 3, Cout,eff >= 10 x L,eff). PS/SYNC високо = PFM при малък товар (~50 uA).

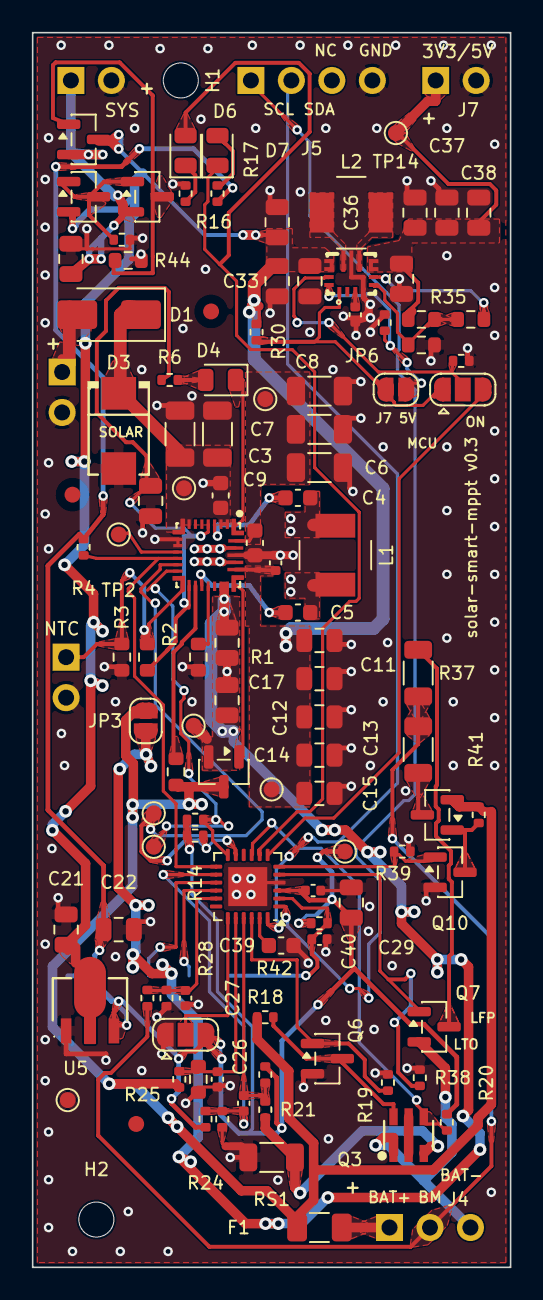
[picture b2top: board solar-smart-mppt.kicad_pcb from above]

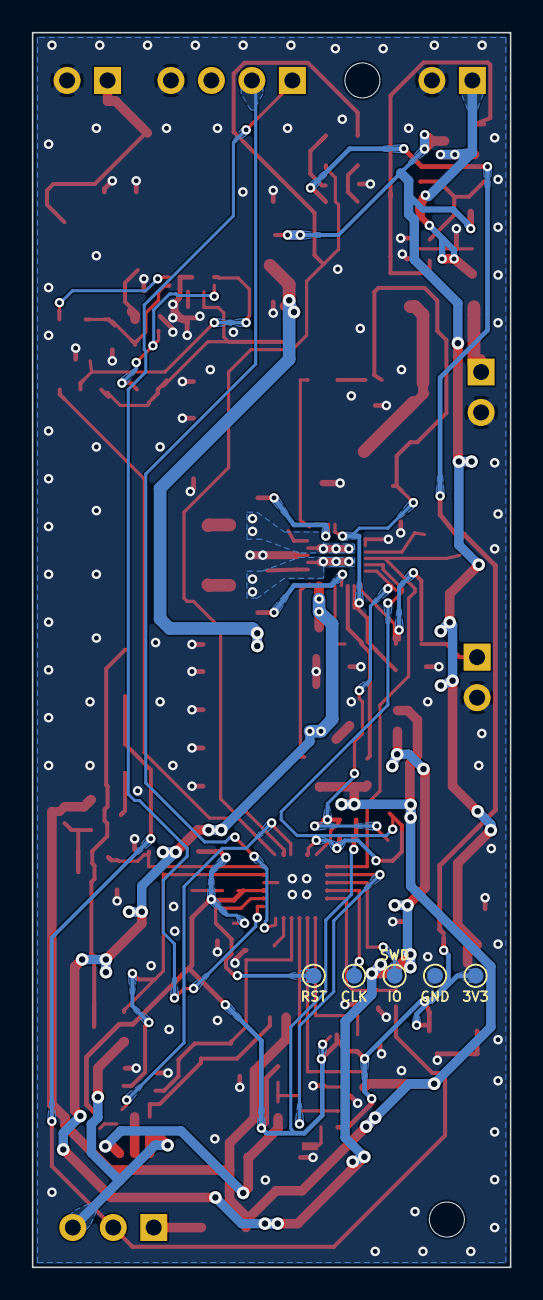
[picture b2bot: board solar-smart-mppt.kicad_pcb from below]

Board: 2 copper layers, 30.0 x 77.5 mm, 124 parts (5 on the bottom side), 64 nets.

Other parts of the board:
FID1, FID2, FID3: Fiducial; Fiducial_1mm_Mask2mm

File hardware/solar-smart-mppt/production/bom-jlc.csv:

Comment,Designator,Footprint,LCSC
10u/50V,"C1,C2,C6,C7,C8",C_1206_3216Metric,C13585
4.7u/25V,C10,C_0805_2012Metric,C1779
10u/25V,"C11,C12,C13,C14,C15,C17,C18,C20,C21,C22,C29,C31,C32,C33,C35",C_0805_2012Metric,C15850
100n,"C16,C24,C26,C27,C28,C34",C_0402_1005Metric,C1525
100n,"C3,C9",C_0603_1608Metric,C14663
22u/25V,"C36,C37,C38",C_0805_2012Metric,C45783
470n,C39,C_0603_1608Metric,C1623
47n,"C4,C5",C_0603_1608Metric,C1622
10n,C40,C_0402_1005Metric,C15195
SS54,D1,D_SMA,C22452
SMBJ24A,D3,SMB_L4.6-W3.6-LS5.3-RD,C19077578
green,D4,LED_0805_2012Metric,C2297
red ERR,D6,LED_0805_2012Metric,C84256
yellow BMS,D7,LED_0805_2012Metric,C2296
3A 1206 (0468003),F1,Fuse_1206_3216Metric,C41342
2.2uH 4A molded (MWSA0402S),"L1,L2",IND-SMD_L4.4-W4.2_MWSA0402S,C408335
AO3400A (ship FET),Q2,SOT-23,C20917
HJ8205,Q3,SOT-23-6_L2.9-W1.6-P0.95-LS2.8-BL,C20069150
AO3401A,"Q5,Q8",SOT-23,C15127
2N7002,"Q6,Q7,Q10",SOT-23,C8545
MMBT3906,"Q9,Q11",SOT-23,C7420354
4.7k 1%,R1,R_0603_1608Metric,C23162
4.7k,"R13,R14",R_0402_1005Metric,C25900
5.1k 1%,R2,R_0603_1608Metric,C23186
10k,"R21,R22,R30",R_0402_1005Metric,C25744
30k 1%,R3,R_0603_1608Metric,C22984
150k 1%,R34,R_0603_1608Metric,C22807
220k 1%,R35,R_0603_1608Metric,C22961
100 1206,"R37,R41",R_1206_3216Metric,C17901
100k,"R4,R19,R38,R39,R40",R_0402_1005Metric,C25741
47k,R42,R_0402_1005Metric,C25792
1M,"R18,R20,R23,R24,R25,R27,R28,R31,R32,R43",R_0402_1005Metric,C26083
470k,"R26,R33,R44",R_0603_1608Metric,C23178
2.2k,"R6,R16,R17",R_0402_1005Metric,C25879
100,R8,R_0603_1608Metric,C22775
20m 1W 1%,RS1,R_1206_3216Metric,C163047
BQ25798RQMR,U1,QFN-29_L4.0-W4.0-P0.40-TL-BQ25792RQMR,C2876593
MSPM0L1306SRGER,U4,VQFN-24-1EP_4x4mm_P0.5mm_EP2.45x2.45mm,C19189323
HT7533-1,U5,SOT-89-3_L4.5-W2.5-P1.50-LS4.2-BR,C14289
TPS63070RNMR,U6,VQFN-15_L3.0-W2.5-P0.50-BL,C109322

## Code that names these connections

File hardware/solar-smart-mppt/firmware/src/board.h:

// solar-smart-mppt v0.3 pins (J5 on PA0/PA1, OC_G on PA10) (MSPM0L1306SRGER, VQFN-24). IOMUX index = PINCM(n) = PA(n-1).
#pragma once
#include <ti/devices/msp/msp.h>
#include <ti/driverlib/driverlib.h>

// I2C0 target on J5 (INA260 0x41 + our map 0x42), 3.3 V bus, pull-ups on the repeater.
// PA0/PA1 are open-drain (fail-safe: no diode to VDD) and are the ROM BSL's I2C pins.
#define PIN_SDA_E_IOMUX  IOMUX_PINCM1      // PA0
#define PIN_SDA_E_FUNC   IOMUX_PINCM1_PF_I2C0_SDA
#define PIN_SCL_E_IOMUX  IOMUX_PINCM2      // PA1
#define PIN_SCL_E_FUNC   IOMUX_PINCM2_PF_I2C0_SCL

// I2C1 controller to the BQ25798 (R13/R14 4.7k)
#define PIN_SCL_I_IOMUX  IOMUX_PINCM16     // PA15
#define PIN_SCL_I_FUNC   IOMUX_PINCM16_PF_I2C1_SCL
#define PIN_SDA_I_IOMUX  IOMUX_PINCM17     // PA16 (also the OPA1 output pin: keep that off)
#define PIN_SDA_I_FUNC   IOMUX_PINCM17_PF_I2C1_SDA

// digital
#define PIN_OC_G      DL_GPIO_PIN_10       // R20 pull-up to 3V3M: low = charge FET off, high = on
#define PIN_OC_G_IOMUX IOMUX_PINCM11
#define PIN_BAL1      DL_GPIO_PIN_2        // cell 1 bleed (Q7)
#define PIN_BAL1_IOMUX IOMUX_PINCM3
#define PIN_BAL2      DL_GPIO_PIN_3        // cell 2 bleed (Q10 -> Q8)
#define PIN_BAL2_IOMUX IOMUX_PINCM4
#define PIN_J7        DL_GPIO_PIN_4        // REG_CTL, J7 EN through JP5 2-3
#define PIN_J7_IOMUX  IOMUX_PINCM5
#define PIN_LED       DL_GPIO_PIN_9        // high = red D6, low = yellow D7, Hi-Z = off
#define PIN_LED_IOMUX IOMUX_PINCM10
#define PIN_CE        DL_GPIO_PIN_17       // ~CE: high = no charging (R4 pull-up)
#define PIN_CE_IOMUX  IOMUX_PINCM18
#define PIN_CHEM      DL_GPIO_PIN_23       // JP4: open = follows the pull, 1-2 = 0, 2-3 = 1
#define PIN_CHEM_IOMUX IOMUX_PINCM24
#define PIN_OD        DL_GPIO_PIN_26       // OD_CTL high = discharge FET off (Q6)
#define PIN_OD_IOMUX  IOMUX_PINCM27

// analog: SH_P PA25 -> OPA0 IN0+, SH_N PA18 -> OPA1 IN0+, VBAT PA24 = A3 (1M/470k), VBM PA21 = A5 (1M/1M)
#define ADC_CH_OPA0   DL_ADC12_INPUT_CHAN_12
#define ADC_CH_OPA1   DL_ADC12_INPUT_CHAN_13
#define ADC_CH_VBAT   DL_ADC12_INPUT_CHAN_3
#define ADC_CH_VBM    DL_ADC12_INPUT_CHAN_5

#define VBAT_DIV_NUM  1470u                // (1M + 470k) / 470k
#define VBAT_DIV_DEN  470u
#define VBM_DIV       2u                   // 1M / 1M
#define OPA_GAIN      16
#define VREF_MV       2500u

// settings store: two 1 KB sectors at the end of the 64 KB flash (the linker stops before them)
#define STORE_BASE    0x0000F000u

#define MCLK_HZ       4000000u             // SYSOSC at 4 MHz: enough for 100/400 kHz I2C, low current
